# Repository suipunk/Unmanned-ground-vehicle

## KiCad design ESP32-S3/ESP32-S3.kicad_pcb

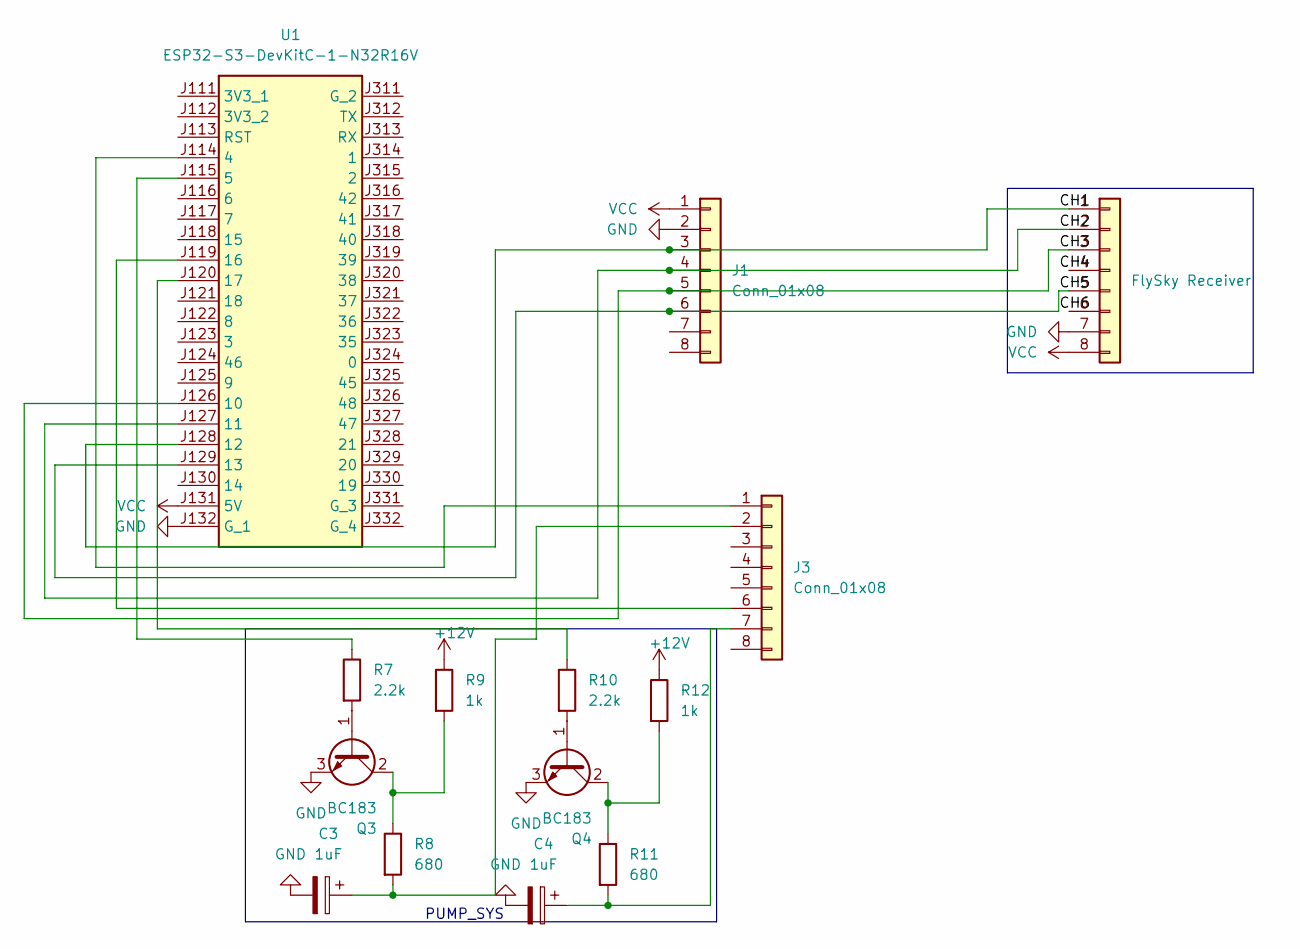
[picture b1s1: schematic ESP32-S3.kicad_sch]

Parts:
C3, C4: 1uF; CP_Radial_D5.0mm_P2.00mm
J1, J3: Conn_01x08; PinHeader_1x08_P2.54mm_Vertical
J2: FlySky Receiver; PinHeader_1x08_P2.54mm_Vertical
Q3, Q4: BC183; TO-92_Inline
R7, R10: 2.2k; R_Axial_DIN0207_L6.3mm_D2.5mm_P10.16mm_Horizontal
R8, R11: 680; R_Axial_DIN0207_L6.3mm_D2.5mm_P10.16mm_Horizontal
R9, R12: 1k; R_Axial_DIN0207_L6.3mm_D2.5mm_P10.16mm_Horizontal
U1: ESP32-S3-DevKitC-1-N32R16V; ESP32S3DevKitC1N32R16V; Manufacturer_Part_Number ESP32-S3-DevKitC-1-N32R16V; Mouser Part Number 356-32S3DKTC1N32R16V

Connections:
+12V: R9.1, R12.1
/CH1: J1.3, J2.1, U1.J128 (12)
/CH2: J1.4, J2.2, U1.J127 (11)
/CH3: J1.5, J2.3, U1.J126 (10)
/CH5: J1.6, J2.5, U1.J129 (13)
GND: C3.2, C4.2, J1.2, J2.7, Q3.3 (E), Q4.3 (E), U1.J132 (G_1)
unnamed: J3.1, U1.J114 (4)
unnamed: C3.1, J3.2, R8.2
unnamed: J3.6, U1.J119 (16)
unnamed: C4.1, J3.7, R11.2
unnamed: Q3.1 (B), R7.2
unnamed: Q3.2 (C), R8.1, R9.2
unnamed: Q4.1 (B), R10.2
unnamed: Q4.2 (C), R11.1, R12.2
unnamed: R7.1, U1.J115 (5)
unnamed: R10.1, U1.J120 (17)
VCC: J1.1, J2.8, U1.J131 (5V)

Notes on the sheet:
PUMP_SYS

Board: 2 copper layers, 14 parts (0 on the bottom side), 17 nets, no tracks yet.

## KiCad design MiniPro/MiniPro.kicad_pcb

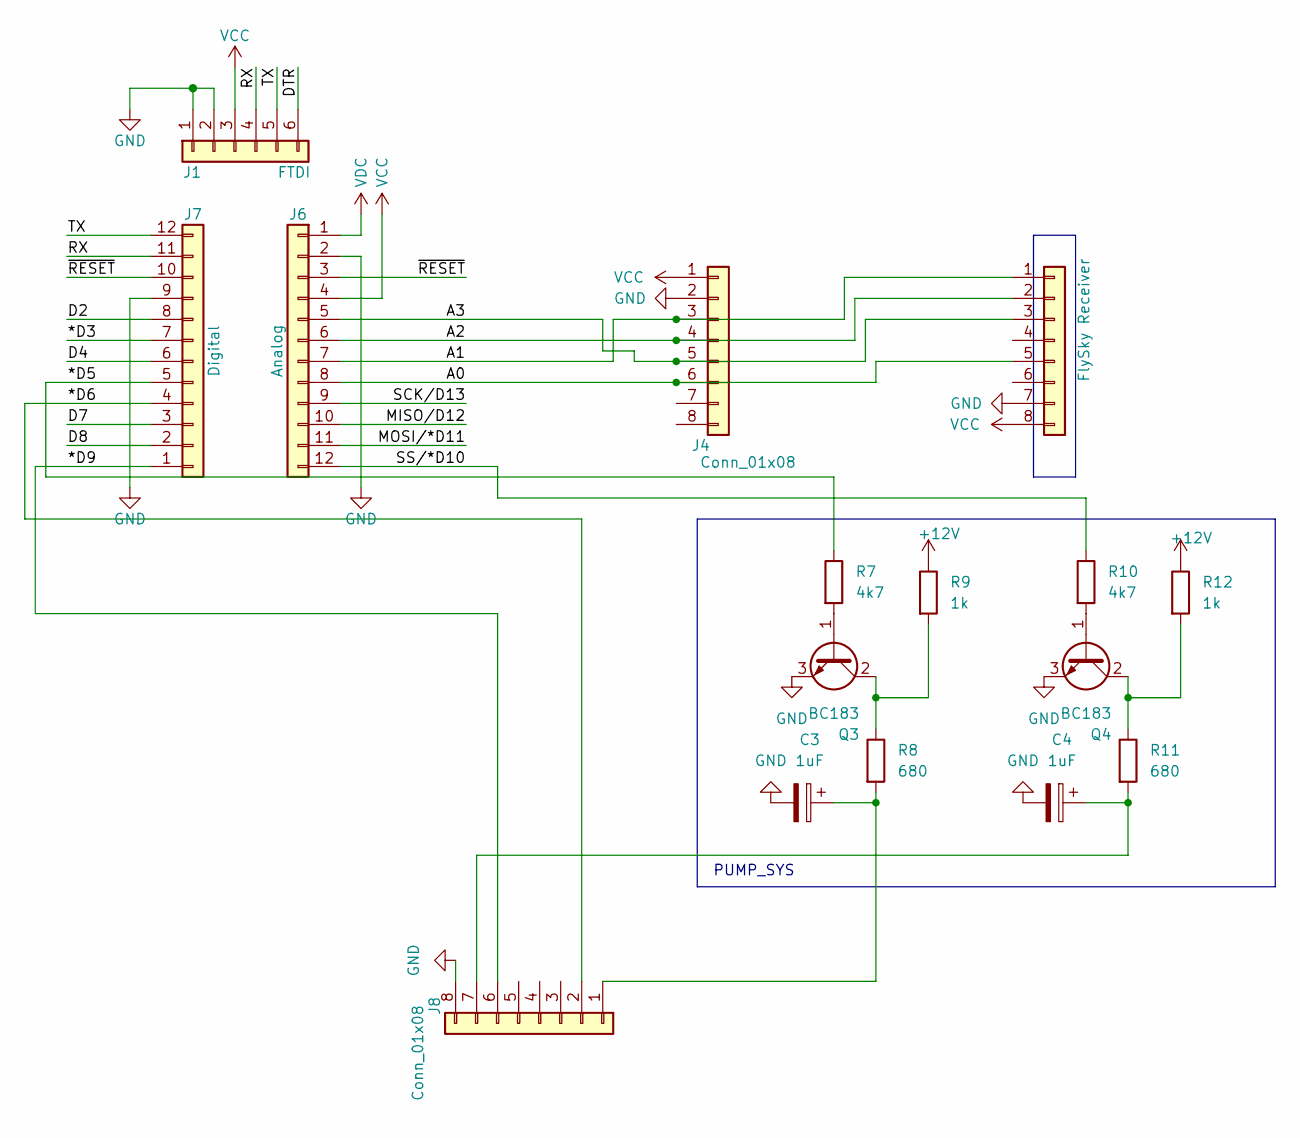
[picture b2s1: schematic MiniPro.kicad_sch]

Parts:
C3, C4: 1uF; CP_Radial_D5.0mm_P2.00mm
J1: FTDI; PinHeader_1x06_P2.54mm_Horizontal
J4, J8: Conn_01x08; PinHeader_1x08_P2.54mm_Vertical
J5: FlySky Receiver; PinHeader_1x08_P2.54mm_Vertical
J6: Analog; PinHeader_1x12_P2.54mm_Vertical
J7: Digital; PinHeader_1x12_P2.54mm_Vertical
Q3, Q4: BC183; TO-92_Inline
R7, R10: 4k7; R_Axial_DIN0207_L6.3mm_D2.5mm_P10.16mm_Horizontal
R8, R11: 680; R_Axial_DIN0207_L6.3mm_D2.5mm_P10.16mm_Horizontal
R9, R12: 1k; R_Axial_DIN0207_L6.3mm_D2.5mm_P10.16mm_Horizontal

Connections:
+12V: R9.1, R12.1
/*D3: J7.7
/*D5: J7.5, R7.1
/*D6: J7.4, J8.2
/*D9: J7.1, J8.6
/A0: J4.6, J5.5, J6.8
/A1: J4.3, J5.1, J6.7
/A2: J4.4, J5.2, J6.6
/A3: J4.5, J5.3, J6.5
/D2: J7.8
/D4: J7.6
/D7: J7.3
/D8: J7.2
/DTR: J1.6
/MISO/D12: J6.10
/MOSI/*D11: J6.11
/RX: J1.4, J7.11
/SCK/D13: J6.9
/SS/*D10: J6.12, R10.1
/TX: J1.5, J7.12
/~RESET: J6.3, J7.10
GND: C3.2, C4.2, J1.1, J1.2, J4.2, J5.7, J6.2, J7.9, J8.8, Q3.3 (E), Q4.3 (E)
unnamed: C3.1, J8.1, R8.2
unnamed: C4.1, J8.7, R11.2
unnamed: Q3.1 (B), R7.2
unnamed: Q3.2 (C), R8.1, R9.2
unnamed: Q4.1 (B), R10.2
unnamed: Q4.2 (C), R11.1, R12.2
VCC: J1.3, J4.1, J5.8, J6.4
VDC: J6.1

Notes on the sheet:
PUMP_SYS

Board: 2 copper layers, 18 parts (2 on the bottom side), 20 nets, no tracks yet.

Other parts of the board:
J2: I2C; PinHeader_1x02_P2.54mm_Vertical
J3: Analog; PinHeader_1x02_P2.54mm_Vertical
